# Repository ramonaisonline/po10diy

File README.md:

# po10diy
A tiny video synthesizer in the pocket operator format

## Background
I made this for the Teenage Engineering #po10diy contest — it's a two-color video synthesizer that has an onboard screen and battery for making video art on the go, and a DVI port so you can plug it into a projector!

You can read the full story behind it on my website: [ramona.diy](https://ramona.diy/video-art/po-video)

## Making your own
I'm not selling these, but this repository includes everything you'd need to make your own! And I encourage that! Please send me pics :)

# Hardware
## Supplies
I estimate that these cost around $100 to build. The most expensive parts of this are:
- The display ($45)
- The microcontroller ($15)
- The PCB (maybe $10-20 depending on where you get it from, how many you order, the tariffs du jour, etc).

### Parts
- 1 x [Adafruit Feather RP2040 with DVI](https://www.adafruit.com/product/5710)
- 1 x [Adafruit 2.7” 400x240 Sharp Memory Display](https://www.adafruit.com/product/4694)
- 2 x [10k potentiometer with built-in knob](https://www.adafruit.com/product/4133)
- 2 x [Breadboard-friendly 3.5mm stereo headphone jack](https://www.adafruit.com/product/1699)
- 1 x [Adafruit 400 mAh LiPo battery](https://www.adafruit.com/product/3898)
- 18 x [Surface-mount tactile switches](https://www.jameco.com/z/TL3301NF160QG-TR-JVP-Jameco-ValuePro-Surface-Mount-Tactile-Pushbutton-Switch-SPST-NO-OFF-MOM-50mA-12VDC-Tape-Reel_2334399.html)
- 18 x [Surface-mount 1N4148 diode](https://www.mouser.com/ProductDetail/Vishay/1N4148W-HG3_A-08?qs=Imq1NPwxi77PuyLGBhrVtQ%3D%3D)
- 2 x [Surface-mount 1.1k resistor](https://www.mouser.com/ProductDetail/Vishay-Beyschlag/MCS04020D1101BE000?qs=bTzheeSci6TjHr/d2PD0oQ%3D%3D)
  - R3 and R4 on the PCB
- 1 x [10.2k Surface-mount resistor](https://www.mouser.com/ProductDetail/Vishay/MCS04020D1022BE000?qs=pUKx8fyJudATYWOpd0Fc/A%3D%3D)
  - R1 on the PCB
- 1 x [15k Surface-mount resistor](https://www.mouser.com/ProductDetail/Vishay-Beyschlag/MCS04020C1502FE500?qs=81r%252BiQLm7BRdp6vG%252BWjYSQ%3D%3D)
  - R2 on the PCB
- 2 x [15 uF Surface-mount capacitor](https://www.mouser.com/ProductDetail/Murata-Electronics/GRM155R60G156ME01D?qs=doiCPypUmgFLObzcgpnt9Q%3D%3D)
  - C1 and C2 on the PCB
- 1 x [Slide switch](https://www.mouser.com/ProductDetail/E-Switch/EGJ1210AAT2?qs=%252BXxaIXUDbq28DPumZsnIIA%3D%3D)
- Standard 0.1” header pins and sockets, specifically:
  - One 12-pin female header
  - One 12-pin male header
  - One 16-pin female header
  - One 16-pin male header
  - One 9-pin male header (for the display)
  - You can buy these in bulk (I just had a bunch lying around), or you can get some from Adafruit, like [this](https://www.adafruit.com/product/2886) and [this](https://www.adafruit.com/product/3002)
- Custom PCB
  - I've uploaded the files for these too, so you can just order them directly
  - More details below
- 4 x M2 or M2.5 10mm machine screw
- 12 x M2 or M2.5 nut

### Tools
- Soldering iron
- Lead-free solder
- Low-temp solder paste
  - I used [Maker Paste](https://www.adafruit.com/product/3217)
- Hot plate
  - I used a TLBZK 100mm x 100mm 350W hot plate from Amazon
- Ventilation fan
- Snips
- Tweezers for positioning small components
- Hobby knife or file for cleaning up rough PCB edges

## PCB
You can order the board from [my shared project on OSHPark](https://oshpark.com/shared_projects/P2hzrhho) — as of August 2025 it costs $61 for 3 copies.

If you'd prefer to order them from a different manufacturer, you can use the exported Gerber files in the PCB Files directory. I believe the existing exports will just work, but if they don't for whatever reason, I've also included the entire KiCAD project. You can find [instructions for exporting the files yourself here](https://jlcpcb.com/help/article/how-to-generate-gerber-and-drill-files-in-kicad-8) (for JLCPCB at least).

## Assembly steps

### 1. Cut or file down any rough edges on the PCB
- Mine came with little spiky protrusions from the manufacturing process, and I just snipped and filed them down

### 2. Unpackage and organize your parts
- The resistors especially are hard to tell apart, so keep everything nice and tidy and don't forget what's what!

### 3. Place the surface-mount diodes, resistors, and capcitors
- Pre-heat the hotplate according to your solder paste (I used Maker Paste and set my hotplate to 145 C)
- Squeeze out little dabs of maker paste on each of the pads for the diodes, resistors, and capacitors (we'll do the tactile switches in a separate step)
  - Some of these pads are quite small, so it can help to use a toothpick to scrape out little blobs of paste and wipe them where you want them, rather than squeezing from the tube directly onto the PCB
- Use small amounts of paste, and be especially cautious with the pads for the tiny resistors and capacitors, as they can easily form bridges when too much solder paste is used
- Use tweezers to position the diodes, resistors, and capacitors into their respective places one by one, and gently press them into the paste
  - R1 is the 10.2k resistor
  - R2 is the 15k resistor
  - R3 and R4 are the 1.1k resistors
  - The capacitors are identical but go in the spots marked C1 and C2
  - The diodes are also interchangeable but make sure the stripe on the diode is facing INTO the "C" shaped silkscreen marking, not away from it

### 4. Solder the diodes, resistors, and capacitors
- With the components all placed, put the PCB on the hotplate and let it melt the solder
- First you'll see the paste blobs spread out as the paste warms
- Then the liquid-y flux will boil off
- Then the solder balls in the paste will melt and reflow onto the pads, hopefully avoiding the solder mask
- This process takes a minute or two depending on the temperature
- Ideally you should see your components slide and adjust into place from the surface tension of the solder
- Watch carefully to make sure the solder paste is all melting at roughly the same time
  - If the board isn't sitting totally flat, press it down with a scredriver or tweezers to make sure it's heating evenly
- Look for any solder bridges that might have formed around the smallest components, and use tweezers or a craft knife to very gently remove some of the solder or smush it around until it separates again from the solder mask

### 5. Let the PCB cool
- It will be quite hot, so remove the PCB with tweezers or something similar and let it cool down and rest on a heat-safe surface
- Let it cool completely, to make the next step easier

### 6. Place the tactile switches
- Make sure the hot plate is preheating again if you shut it off earlier
- Like before, squeeze out solder blobs onto all the pads of the 18 tactile switches (though this time it will be a little easier to not make a mess since the pads are larger and further apart)
- Use tweezers to position the tactile switches on the blobs of solder paste

### 7. Solder the tactile switches
- Like before, put the PCB on the hotplate
  - I tried to have the top third of the PCB hanging off the plate so that the smaller components didn't heat up again, just in case their positioning got messed up, but I don't know how much of a difference this makes
- Wait a minute or two for the paste to melt and attach the switches

### 8. Let the PCB cool
- It's hot! Be careful!

### 9. Flip the board over and solder the 12 and 16 pin female header strips to the underside of the board
- The microcontroller will go on the back
- Strictly speaking you don't need the female header here, you could solder the feather to the circuit board directly with male header, but the female header makes it removable in case you want to use it for something else later, and it makes room for the battery to go underneath
- Trim the leads if they're long on the front side, the display will go above them and there's only so much room

### 10. Solder the 12 and 16 pin male header strips to the Feather
- The header should point "down" (i.e. the longer part should protrude from the flat bottom of the Feather), and you should be soldering it from the top of the Feather
- I like to just plug the male header into the female header we just soldered, then drop the Feather on top of that and solder — it holds everything in place!

### 11. Solder the audio jacks to the back of the board
- You may have to press quite firmly to get all five pins to slide into the holes at once, or even bend them a bit to align better

### 12. Solder the slide switch to the front of the board
- It's slim enough to fit under the display, so you can mount it on the front
- Note that when I designed the PCB I hooked up this switch backwards, so you slide it "down" / towards you to turn it on

### 13. Solder the potentiometers
- You may have to bend the side tabs in slightly to get them to align with the holes
- Double check the tilt of the potentiometers by looking at them from the side. It's easy for them to slightly lean one direction or the other.

### 14. At this point, you can test!
- Upload the code to the Feather using the procedure below to test the device with an external projector / monitor / TV and verify that the buttons and pots all work as expected
- This step is optional, but it's much easier to fix any issues with the diodes / resisotrs / capacitors now, before you solder the display on
- At a minimum, check the connections with a thorough visual inspection and maybe even with a multimeter
- Make sure there are no shorts from excess solder, and that all the components are fully and securely attached

### 15. Solder the male header to the display
- But do NOT solder it to rest of the PCB yet! That will be our final step because it depends on a few things being aligned first.

### 16. File down the right inner corner of the display to fit around Pot B
- Note that the lower mounting points of the display have a slight inner radius where they meet the main body of the display PCB
- This will bump into the hard corner of Pot B and make it hard to align the display properly
- With a craft knife or a file, you can shave down that inner corner radius to a right angle
- You may also need to file down the part of plastic casing of the potentiometers that faces the display a bit to get it to slide smoothly past them

### 17. Mount the display
- Thread bolts through the four mounting holes of the display
- If using M2 bolts, thread two nuts on each of the bolts to provide even spacing between the display and the main PCB
- If using M2.5 bolts, thread nuts only on the upper left, upper right, and lower left bolts (the nuts are too big to sit next to the pots)
- Mount the display to the main PCB using four more nuts
  - The already-soldered male header should be poking through the holes on the main PCB now

### 18. Solder the display
- Almost done! You can test it now if you Like

### 19. Install the battery
- Now, you can plug in the LiPo battery and tuck it under the feather
- It helps to secure it with a piece of tape or something like that

# Software
I've included the Arduino code that I used on my version, with all the drawing functions and everything. Feel free to modify it to your liking! I've included a template layer function in the layers.ino file along with some instructions about how to use the buttons / pot values / etc.

## Flashing the Feather
I recommend follow Adafruit's detailed setup steps:
- [Setting up the Arduino IDE for RP2040 boards](https://learn.adafruit.com/adafruit-feather-rp2040-dvi/arduino-ide-setup)
- [Loading sketches onto the Feather RP2040](https://learn.adafruit.com/adafruit-feather-rp2040-dvi/arduino-usage)
  - The Feather has a UF2 bootloader which means it should be able to put itself into a special mode where it acts as a USB drive and the Arduino IDE can just drop a file on it to load the compiled sketch -- you SHOULD be able to just click "Upload" in the Arduino IDE and it should just work
  - However, I've never gotten that to work consistently, for whatever reason
  - Instead I follow the manual bootloader steps at the bottom of that page, and it works very reliably
  - That does make it slightly more annoying to use the serial monitor because sometimes you have to switch the selected board in the Arduino IDE and close / open the serial monitor panel to get messages to come through
  - All that is to say, YMMV, and try it both ways!
- [All about the PicoDVI library for the Feather](https://learn.adafruit.com/picodvi-arduino-library-video-out-for-rp2040-boards)
- [Drawing shapes with Adafruit GFX](https://learn.adafruit.com/adafruit-gfx-graphics-library/graphics-primitives)

## Remaining TODOs
A few small features left to implement here!
- The PO Sync feature (the PCB should be set up for it)
- Creating / swapping between different sequences (the folder button)
- Switch layers without triggering them via the layer buttons
- Change tempo

# Using it
TODO: Quick user manual

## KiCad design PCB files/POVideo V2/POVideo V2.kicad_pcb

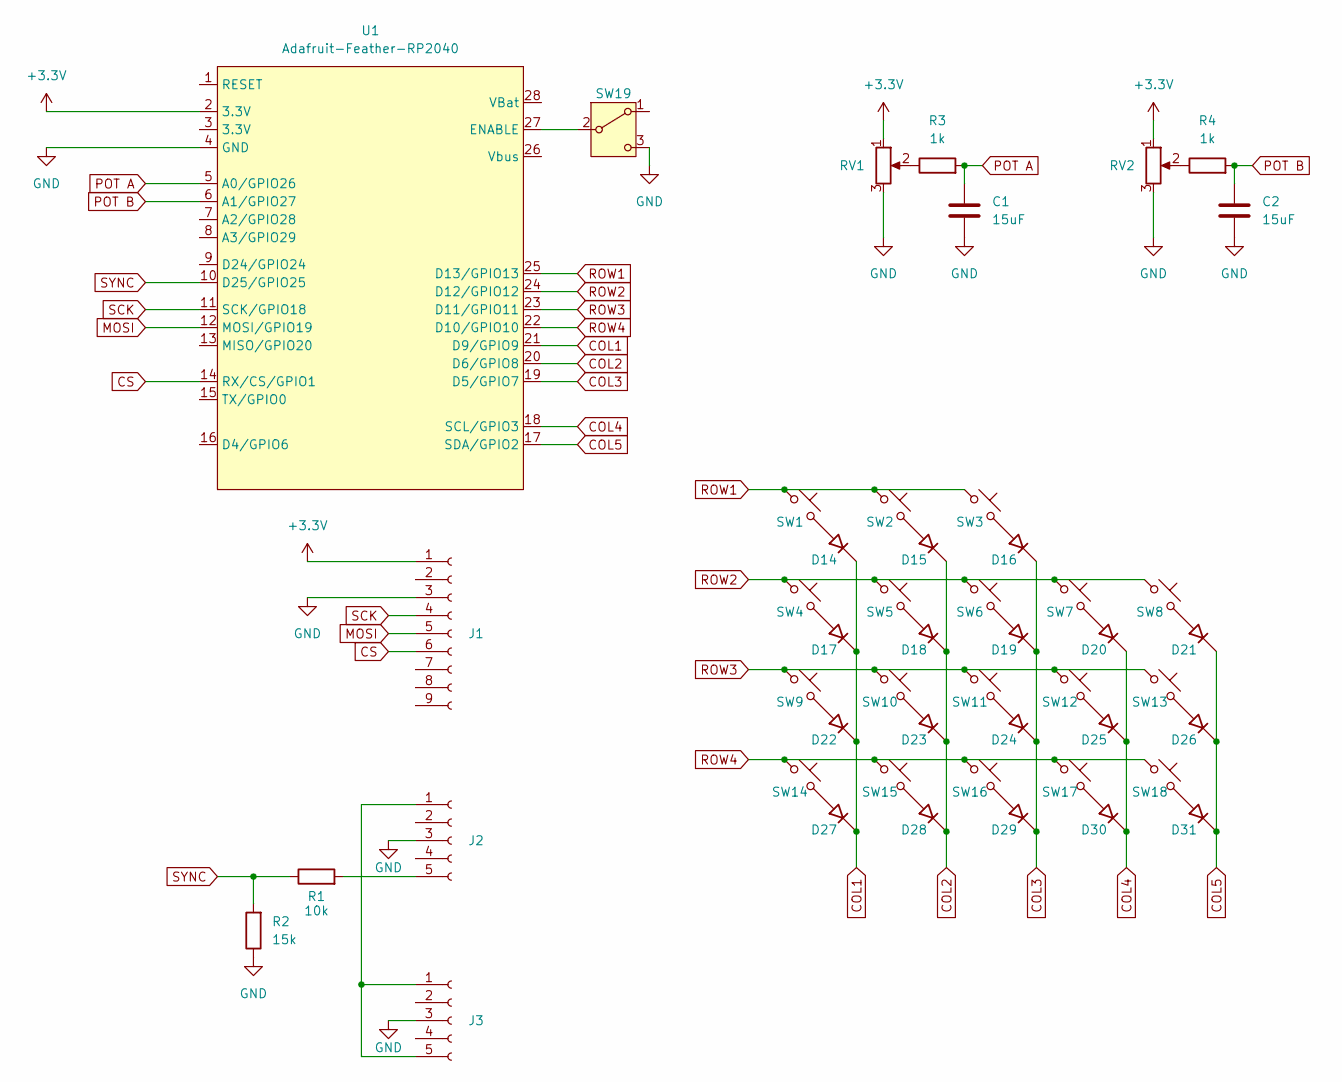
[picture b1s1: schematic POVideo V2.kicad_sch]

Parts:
C1, C2: 15uF; C_0402_1005Metric
D14, D15, D16, D17, D18, D19, D20, D21, D22, D23, D24, D25, D26, D27, D28, D29, D30, D31: D_45deg; D_SOD-123
J1: Conn_01x05_Socket; PinHeader_1x09_P2.54mm_Vertical
J2, J3: Conn_01x05_Socket; 5 pin headphone jack
R1: 10k; R_0402_1005Metric
R2: 15k; R_0402_1005Metric
R3, R4: 1k; R_0402_1005Metric
RV1, RV2: R_Potentiometer; Adafruit Potentiometer
SW1, SW2, SW3, SW4, SW5, SW6, SW7, SW8, SW9, SW10, SW11, SW12, SW13, SW14, SW15, SW16, SW17, SW18: SW_Push_45deg; TL3301 6mm tactile switch
SW19: SW_SPST; Right Angle Slide Switch
U1: Adafruit-Feather-RP2040; Adafruit_Feather

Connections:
+3.3V: J1.1, RV1.1, RV2.1, U1.2 (3.3V)
COL1: D14.1 (K), D17.1 (K), D22.1 (K), D27.1 (K), U1.21 (D9/GPIO9)
COL2: D15.1 (K), D18.1 (K), D23.1 (K), D28.1 (K), U1.20 (D6/GPIO8)
COL3: D16.1 (K), D19.1 (K), D24.1 (K), D29.1 (K), U1.19 (D5/GPIO7)
COL4: D20.1 (K), D25.1 (K), D30.1 (K), U1.18 (SCL/GPIO3)
COL5: D21.1 (K), D26.1 (K), D31.1 (K), U1.17 (SDA/GPIO2)
CS: J1.6, U1.14 (RX/CS/GPIO1)
GND: C1.2, C2.2, J1.3, J2.3, J3.3, R2.1, RV1.3, RV2.3, SW19.3 (C), U1.4 (GND)
LED_DATA: U1.16 (D4/GPIO6)
MOSI: J1.5, U1.12 (MOSI/GPIO19)
unnamed: D14.2 (A), SW1.2
unnamed: D15.2 (A), SW2.2
unnamed: D16.2 (A), SW3.2
unnamed: D17.2 (A), SW4.2
unnamed: D18.2 (A), SW5.2
unnamed: D19.2 (A), SW6.2
unnamed: D20.2 (A), SW7.2
unnamed: D21.2 (A), SW8.2
unnamed: D22.2 (A), SW9.2
unnamed: D23.2 (A), SW10.2
unnamed: D24.2 (A), SW11.2
unnamed: D25.2 (A), SW12.2
unnamed: D26.2 (A), SW13.2
unnamed: D27.2 (A), SW14.2
unnamed: D28.2 (A), SW15.2
unnamed: D29.2 (A), SW16.2
unnamed: D30.2 (A), SW17.2
unnamed: D31.2 (A), SW18.2
unnamed: J2.1, J3.1, J3.5
unnamed: J2.5, R1.2
unnamed: R3.1, RV1.2
unnamed: R4.1, RV2.2
unnamed: SW19.2 (B), U1.27 (ENABLE)
POT A: C1.1, R3.2, U1.5 (A0/GPIO26)
POT B: C2.1, R4.2, U1.6 (A1/GPIO27)
ROW1: SW1.1, SW2.1, SW3.1, U1.25 (D13/GPIO13)
ROW2: SW4.1, SW5.1, SW6.1, SW7.1, SW8.1, U1.24 (D12/GPIO12)
ROW3: SW9.1, SW10.1, SW11.1, SW12.1, SW13.1, U1.23 (D11/GPIO11)
ROW4: SW14.1, SW15.1, SW16.1, SW17.1, SW18.1, U1.22 (D10/GPIO10)
SCK: J1.4, U1.11 (SCK/GPIO18)
SYNC: R1.1, R2.2, U1.10 (D25/GPIO25)

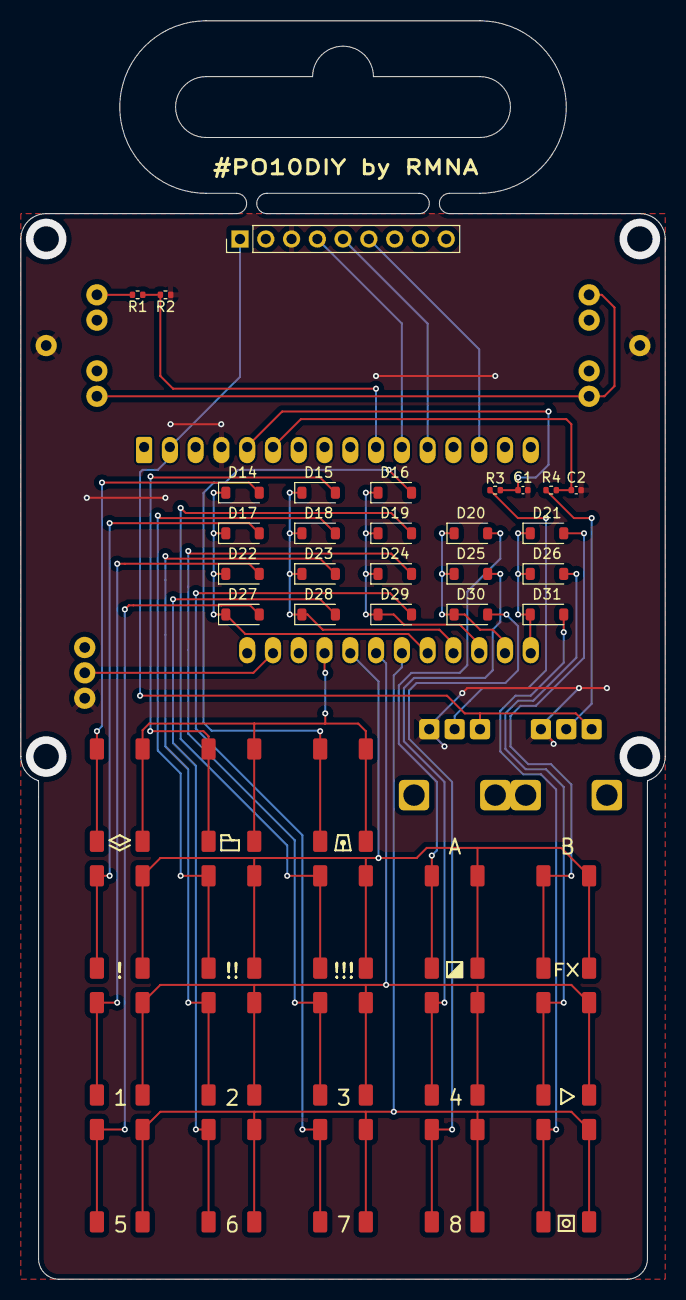
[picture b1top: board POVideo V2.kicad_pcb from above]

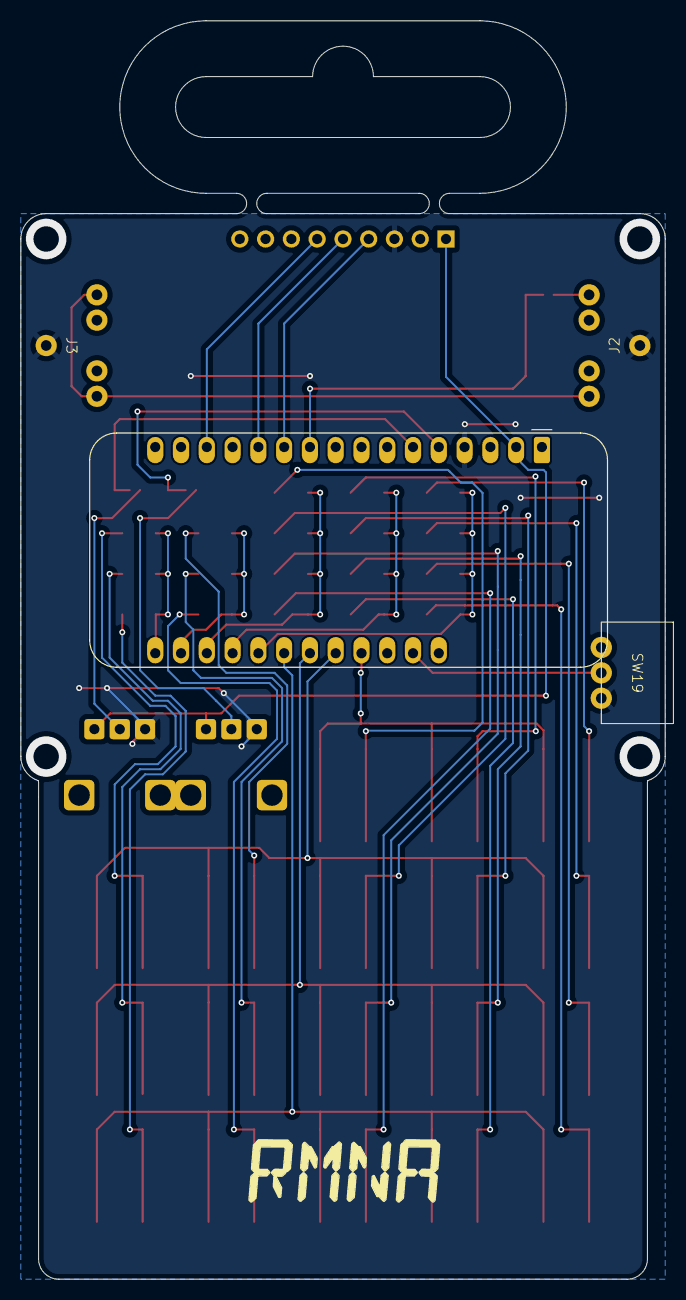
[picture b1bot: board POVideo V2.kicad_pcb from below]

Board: 2 copper layers, 63.5 x 124.0 mm, 49 parts (4 on the bottom side), 40 nets.

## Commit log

2025-08-14 Initial readme commit
2025-08-14 Added some assembly steps to the readme
2025-08-14 Formatting
2025-08-14 Formatting again
2025-08-14 First draft of assembly steps
2025-08-26 Add arduino files
2025-08-26 README updates to finish assembly instructions and add instructions about uploading sketches
2025-08-26 Extra links
2025-08-26 Convert fx to use helpers
2025-08-26 Add KiCAD project and exported gerbers
2025-08-26 Add notes about PCB
2025-08-26 Intro
